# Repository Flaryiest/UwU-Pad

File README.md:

# UwUPad
UwUPad is a 10 key macropad with 4 LEDs.  
This was my first time both CADing and designing a PCB and was a lot of fun!  

## Features 
4 SK6812Minis for RBG Lighting throughout the case  
10 Keys  
KMK Firmware  

## Cad Model  

## PCB  

## Case  

## BOM  
| Component                | Quantity |
| ------------------------ | --       |
| Seeed Studio XIAO RP2040 | 1        |
| 3D printed case          | 1        |
| 1N4148 Diodes            | 10       |
| SK6812Mini LEDs          | 4        |
| M3x16mm Screws           | 4        |
| M3 Hex nuts              | 4        |

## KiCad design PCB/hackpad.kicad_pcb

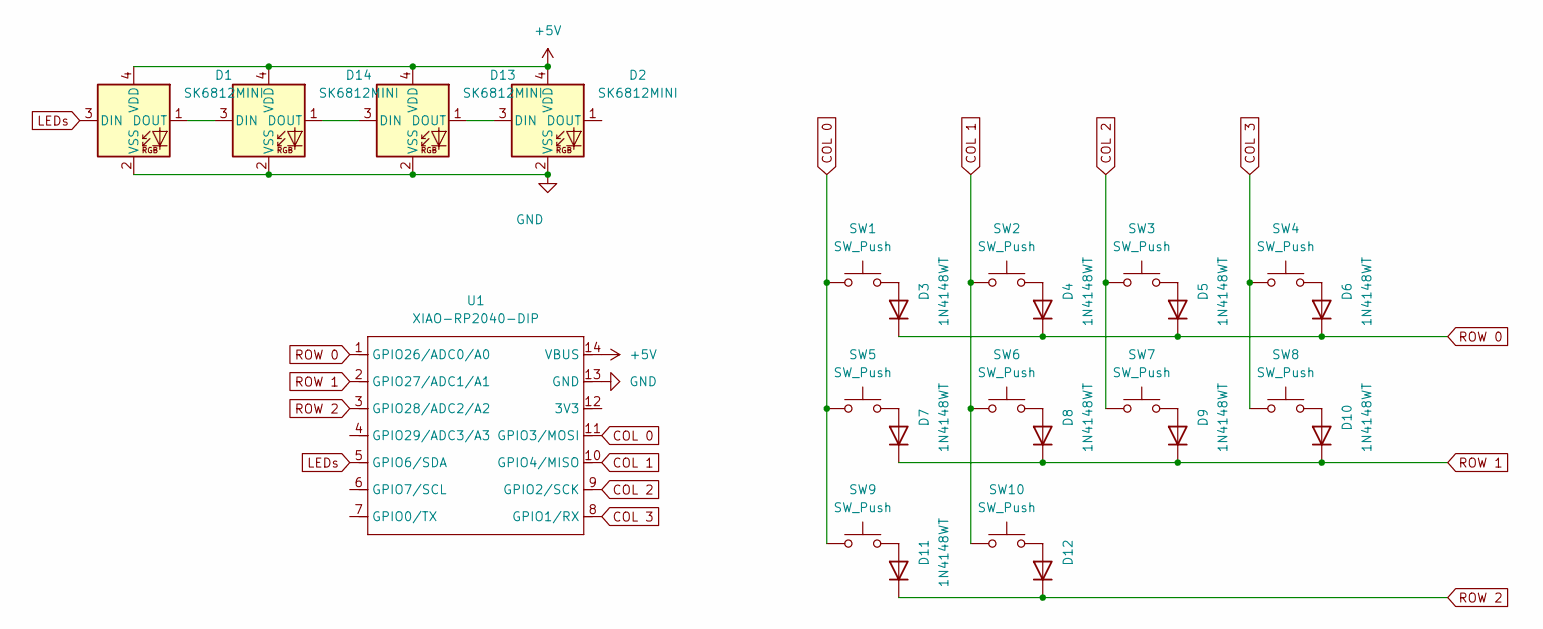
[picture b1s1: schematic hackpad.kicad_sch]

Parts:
D1, D2, D13, D14: SK6812MINI; LED_SK6812MINI_PLCC4_3.5x3.5mm_P1.75mm
D3, D4, D5, D6, D7, D8, D9, D10, D11, D12: 1N4148WT; D_SOD-523
SW1, SW2, SW3, SW4, SW5, SW6, SW7, SW8, SW9, SW10: SW_Push; SW_Cherry_MX_1.00u_PCB
U1: XIAO-RP2040-DIP

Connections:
+5V: D1.4 (VDD), D2.4 (VDD), D13.4 (VDD), D14.4 (VDD), U1.14 (VBUS)
COL 0: SW1.1, SW5.1, SW9.1, U1.11 (GPIO3/MOSI)
COL 1: SW2.1, SW6.1, SW10.1, U1.10 (GPIO4/MISO)
COL 2: SW3.1, SW7.1, U1.9 (GPIO2/SCK)
COL 3: SW4.1, SW8.1, U1.8 (GPIO1/RX)
GND: D1.2 (VSS), D2.2 (VSS), D13.2 (VSS), D14.2 (VSS), U1.13 (GND)
LEDs: D1.3 (DIN), U1.5 (GPIO6/SDA)
unnamed: D1.1 (DOUT), D14.3 (DIN)
unnamed: D3.2 (A), SW1.2
unnamed: D4.2 (A), SW2.2
unnamed: D5.2 (A), SW3.2
unnamed: D6.2 (A), SW4.2
unnamed: D7.2 (A), SW5.2
unnamed: D8.2 (A), SW6.2
unnamed: D9.2 (A), SW7.2
unnamed: D10.2 (A), SW8.2
unnamed: D11.2 (A), SW9.2
unnamed: D12.2 (A), SW10.2
unnamed: D13.3 (DIN), D14.1 (DOUT)
unnamed: D2.3 (DIN), D13.1 (DOUT)
ROW 0: D3.1 (K), D4.1 (K), D5.1 (K), D6.1 (K), U1.1 (GPIO26/ADC0/A0)
ROW 1: D7.1 (K), D8.1 (K), D9.1 (K), D10.1 (K), U1.2 (GPIO27/ADC1/A1)
ROW 2: D11.1 (K), D12.1 (K), U1.3 (GPIO28/ADC2/A2)

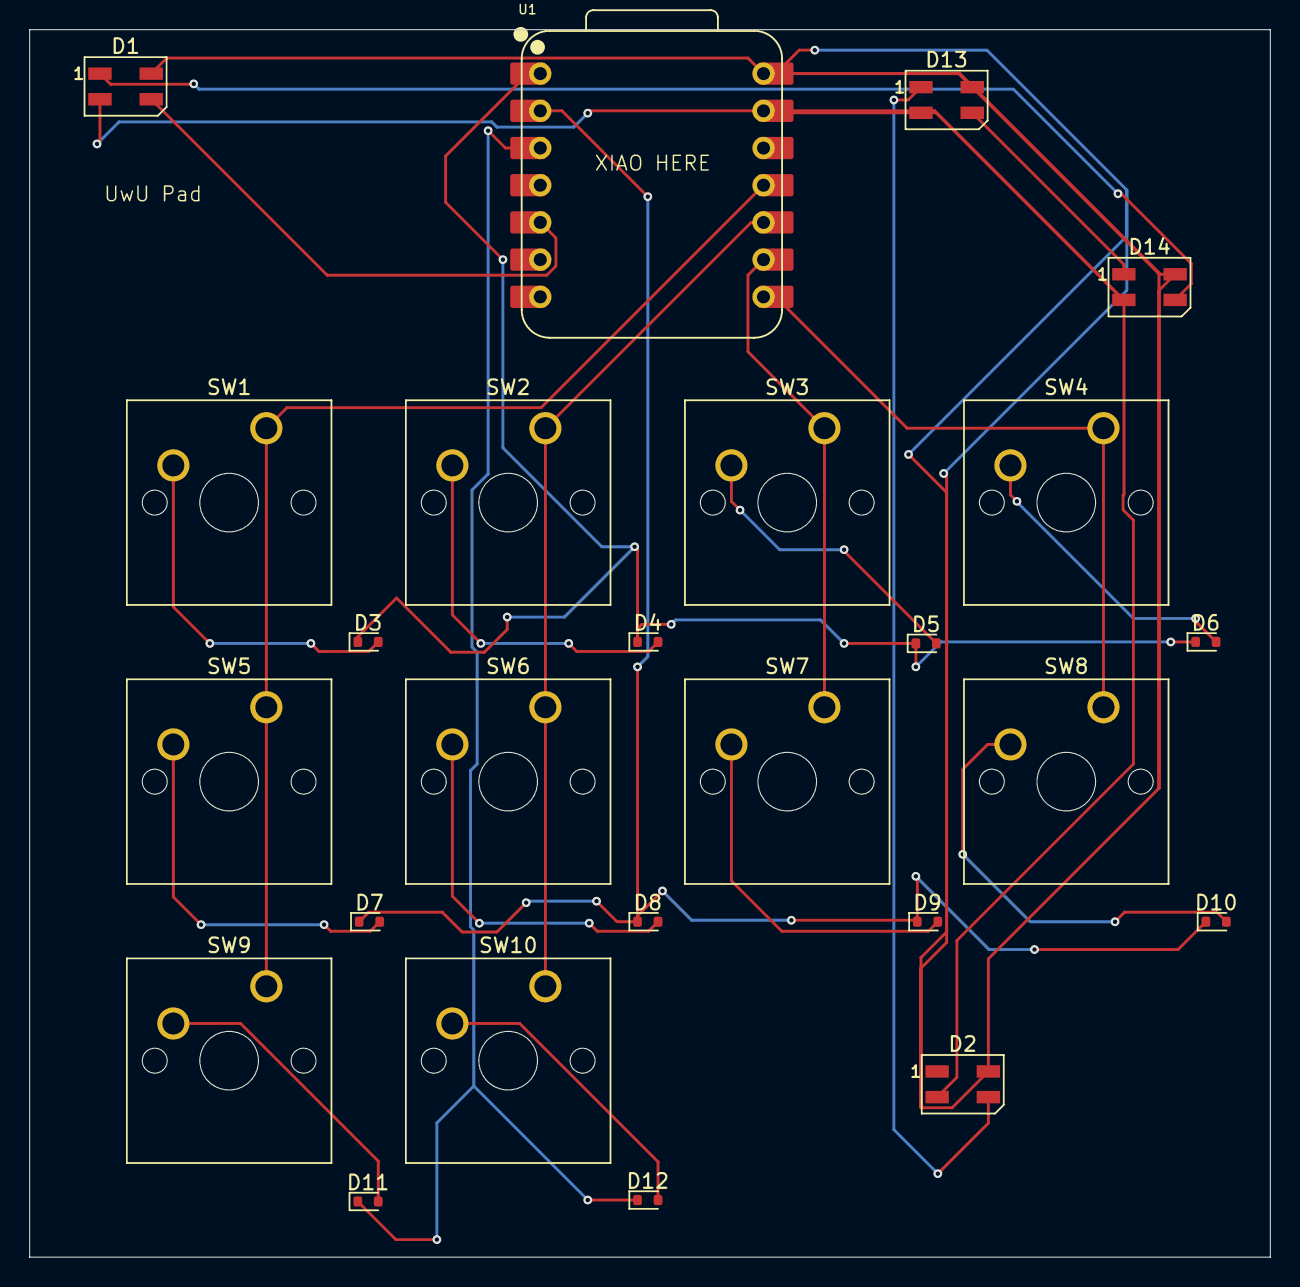
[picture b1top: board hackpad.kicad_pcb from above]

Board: 2 copper layers, 84.7 x 83.8 mm, 25 parts (0 on the bottom side), 23 nets.

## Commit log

2025-05-30 added pcb files
2025-05-30 added CAD of whole hackpad
2025-05-30 added CADs of top and bottom of case
2025-05-31 firmware
2025-05-31 added gerber
